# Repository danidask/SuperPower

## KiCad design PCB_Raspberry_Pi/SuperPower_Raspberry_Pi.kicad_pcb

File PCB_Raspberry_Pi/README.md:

<!-- https://github.com/othneildrew/Best-README-Template -->

<h3 align="center">SuperPower_Raspberry_Pi PCB</h3>

## Table of Contents

- [Table of Contents](#table-of-contents)
- [Usage](#usage)
- [Conventions](#conventions)
- [License](#license)
- [References](#references)
- [Acknowledgements](#acknowledgements)

## Usage

Design with [kicad 5](https://kicad-pcb.org/)

## Conventions

In order to make the BOM jlcpcb compilant, we use a custom python script and some conventions in kicad:

- Each component must have a custom field named "PartNumber" with the lcsc part number
- The components can have a custom field named "Keys" with one special word:
  - DNP  (Do Not Place) This component will not be sent for assambley and will be included in a separated file
  - EXCLUDE This component will not apear in any of the BOM files (ej mounting holes)

To add this custom fields in kicad 5.1:
- Select the component (left click)
- Press "E" to open symbol properties
- Add Field (plus sign)

## License

Distributed under the MIT License. See `LICENSE` for more information.

## References

https://github.com/raspberrypi/hats/

## Acknowledgements

*

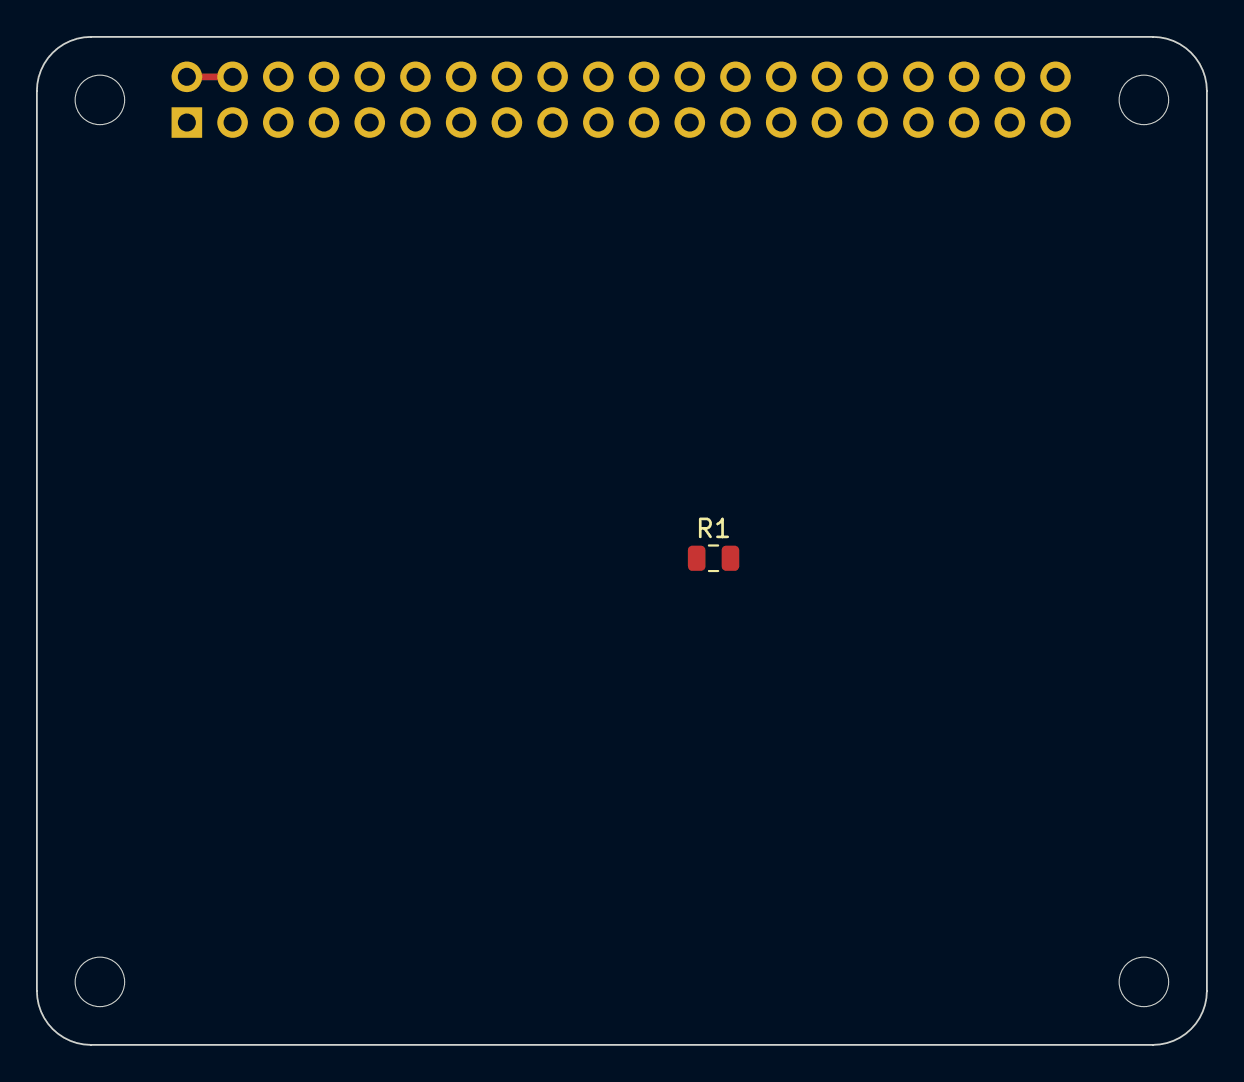
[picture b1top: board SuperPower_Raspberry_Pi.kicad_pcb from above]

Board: 2 copper layers, 65.0 x 56.0 mm, 6 parts (1 on the bottom side), 2 nets.

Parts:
H1, H2, H3, H4: MountingHole; RPi_Hat_Mounting_Hole
J1: RPi_GPIO; PinSocket_2x20_P2.54mm_Vertical
R1: 1k; R_0805_2012Metric

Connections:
+5V: J1.2, J1.4
GND: J1.9, J1.25

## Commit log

2020-09-01 test_library
2020-09-01 library test
2020-09-01 libraries organized
2020-09-03 script for export BOM
